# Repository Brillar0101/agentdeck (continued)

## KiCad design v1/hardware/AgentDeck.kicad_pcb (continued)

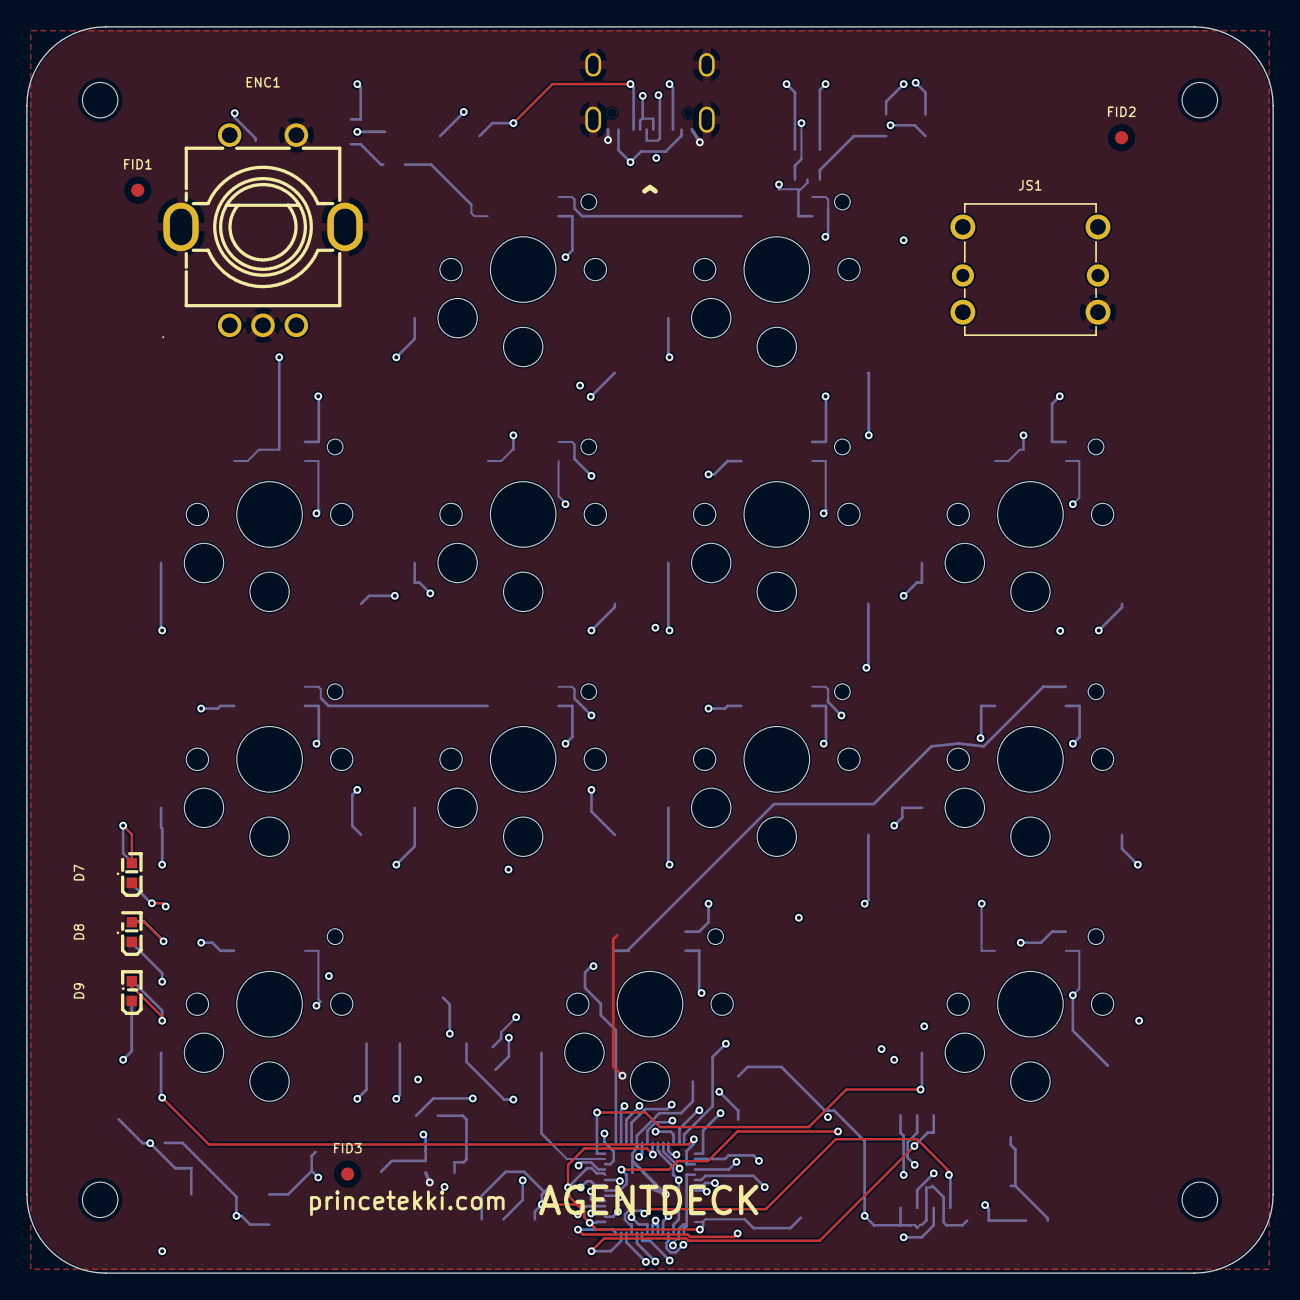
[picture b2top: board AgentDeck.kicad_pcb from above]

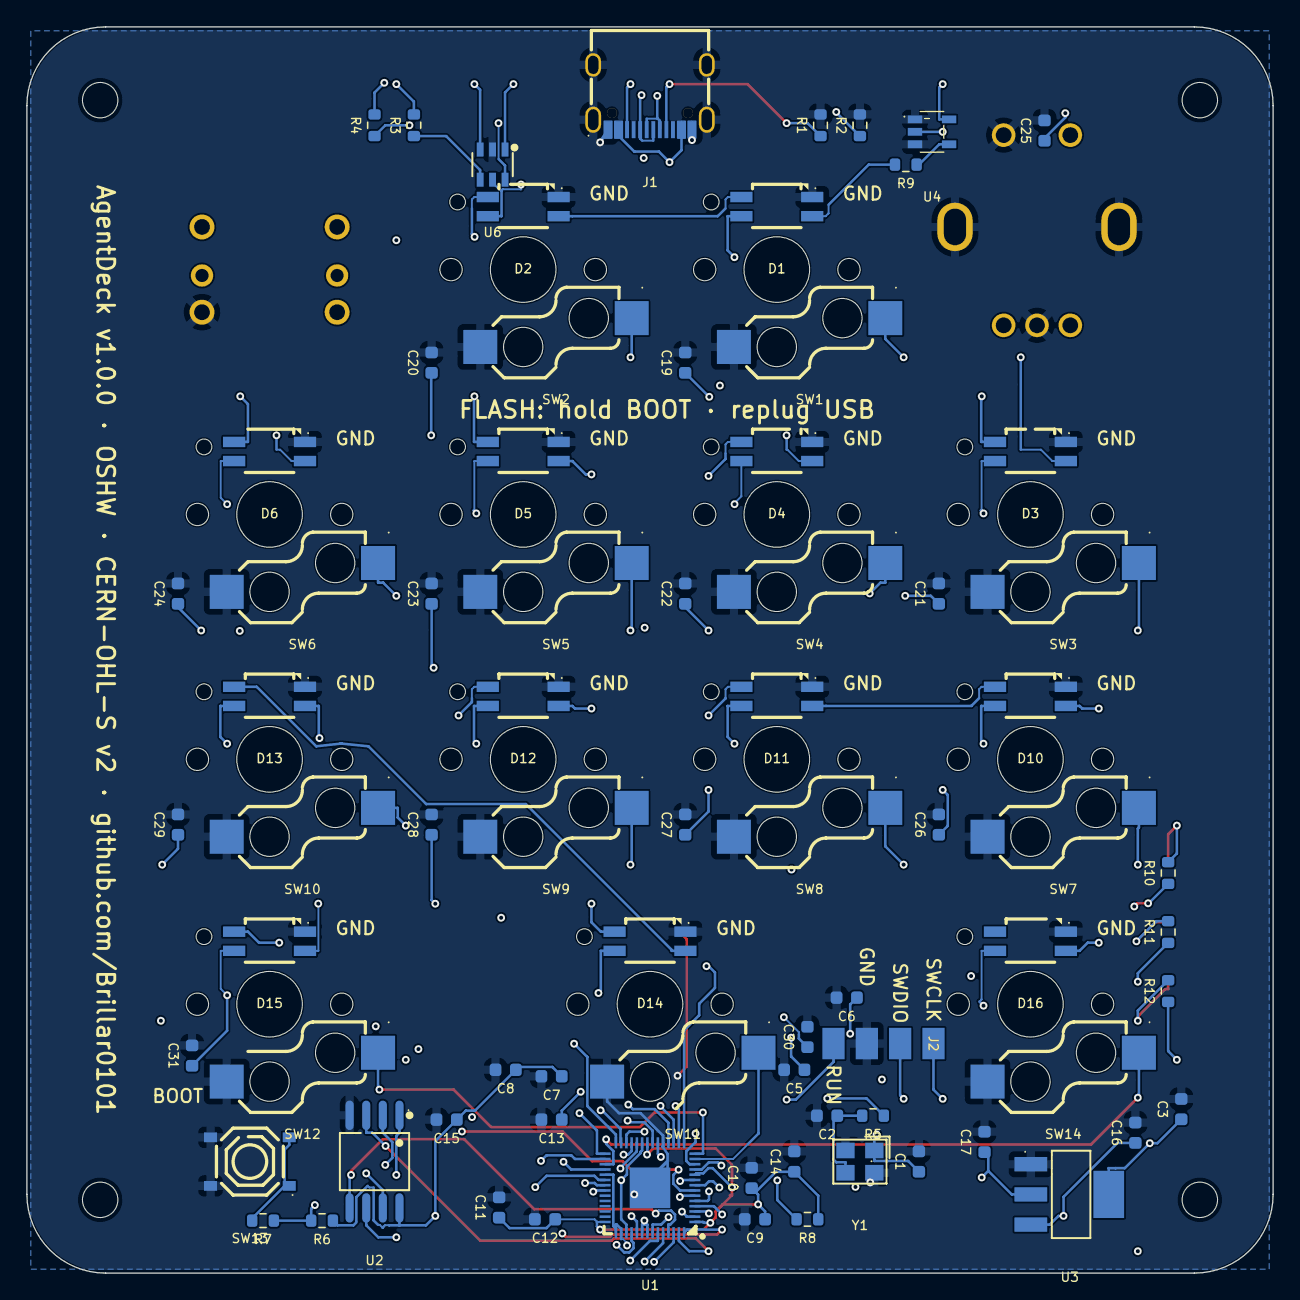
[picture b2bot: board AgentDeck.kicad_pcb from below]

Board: 4 copper layers, 95.0 x 95.0 mm, 101 parts (76 on the bottom side), 67 nets.

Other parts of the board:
D16: LED-SMD_4P-L3.2-W2.8-LS5.9_SK6812MINI-E
FID1, FID2, FID3: Fiducial_1mm_Mask2mm
KEY1, KEY2, KEY3, KEY4, KEY5, KEY6, KEY7, KEY8, KEY9, KEY10, KEY11, KEY12, KEY14: ChocSwitch; KeyOutline
MH1, MH2, MH3, MH4: M2.5; MountingHole_M2.5
SW14: CONN-SMD_HOTPLUGPAKAGE__C9900010116

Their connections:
GND: D16.1, SW14.2; also elsewhere on the board
LED_D13: D16.2; also elsewhere on the board
TOUCH: SW14.1; also elsewhere on the board
VBUS: D16.3; also elsewhere on the board

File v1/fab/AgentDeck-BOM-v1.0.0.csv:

Item,Designators,Qty,Value,Footprint,Supplier,Supplier PN,MPN,Status,Notes
1,"C10,C11,C12,C15,C19,C20,C21,C22,C23,C24,C25,C26,C27,C28,C29,C3,C30,C31,C5,C6,C7,C8,C9",23,100nF 50V X7R,C_0603,LCSC,C14663,CC0603KRX7R9BB104,In cart,
2,"D1,D2,D3,D4,D5,D6,D10,D11,D12,D13,D14,D15,D16",13,SK6812MINI-E RGB,LED-SMD_4P-3.2x2.8,LCSC,C5149201,SK6812MINI-E,In cart,"MOQ 5; ordered 15. Reverse-mount under keycap"
3,"R5,R7,R10,R11,R12",5,1k 1% 0603,R_0603,LCSC,C21190,0603WAF1001T5E,In cart,MOQ 100
4,"D7,D8,D9",3,Red LED 0603,LED-SMD_1.6x0.8,LCSC,C2286,KT-0603R,In cart,
5,"C16,C17",2,10uF 10V X5R 0603,C_0603,LCSC,C19702,CL10A106KP8NNNC,In cart,"MOQ 20. NOT the 0805 C15850 already in cart - package differs"
6,"C1,C2",2,15pF 50V C0G 0603,C_0603,LCSC,C1644,CL10C150JB8NNNC,In cart,MOQ 50. Crystal load caps
7,"C13,C14",2,1uF 0603,C_0603,LCSC,C128624,CC0603KRX5R9BB105,Already in cart,"Equivalent to BOM's C15849 - same value and package"
8,"R3,R4",2,27R 1% 0603,R_0603,LCSC,C25190,0603WAF270JT5E,In cart,"CORRECTED 2026-08-10: old BOM listed C22967 which is 27k - USB would not enumerate"
9,"R1,R2",2,5.1k 1% 0603,R_0603,LCSC,C23186,0603WAF5101T5E,Already in cart,USB-C CC pulldowns
10,R8,1,10k 1% 0603,R_0603,LCSC,C25804,0603WAF1002T5E,In cart - BACKORDERED,0 in stock; substitute any 10k 0603 if it blocks the order
11,R9,1,330R 1% 0603,R_0603,LCSC,C23138,0603WAF3300T5E,In cart,MOQ 100
12,U4,1,74AHCT1G125 buffer,SOT-23-5,LCSC,C7484,SN74AHCT1G125DBVR,In cart,MOQ 5. LED data level shift
13,Y1,1,12MHz crystal,CRYSTAL-SMD_3.2x2.5,LCSC,C20625731,ABM8-272-T3,In cart,MOQ 5
14,U3,1,AMS1117-3.3 LDO,SOT-223-3,LCSC,C6186,AMS1117-3.3,In cart,"MOQ 5. NOT the ME6211 C82942 in cart - different package"
15,SW13,1,Tact switch BOOTSEL,SW-SMD_5.1x5.1,LCSC,C318884,TS-1187A-B-A-B,Already in cart,
16,ENC1,1,EC11 rotary encoder,SW-TH_EC11E1820402,LCSC,C361165,EC11E1834403,In cart,"NOTE: LCSC ships the -1834403 variant; footprint is named for -1820402. Check shaft length against the case"
17,U1,1,RP2040,LQFN-56 7x7,LCSC,C2040,RP2040,In cart,
18,J1,1,USB-C receptacle,TYPE-C-31-M-12,LCSC,C165948,TYPE-C-31-M-12,Already in cart,
19,U6,1,USBLC6-2SC6 ESD,SOT-23-6,LCSC,C7519,USBLC6-2SC6,Already in cart,
20,U2,1,W25Q128JVSIQ 16MB flash,SOIC-8,LCSC,C97521,W25Q128JVSIQ,In cart,
21,"SW1,SW2,SW3,SW4,SW5,SW6,SW7,SW8,SW9,SW10,SW11,SW12,SW14",13,Kailh Choc hot-swap socket,CONN-SMD_HOTPLUGPAKAGE,AliExpress,,CPG135001S30,NOT ON LCSC,"LCSC C5333465 discontinued - 'Not Available'. Kailh Choc V1 sockets, ubiquitous on AliExpress"
22,JS1,1,5-way navigation switch,SKQUCAA010 (THT),AliExpress,,SKQUCAA010,NOT ON LCSC,"Also Newark 59M1983 / Farnell 1435775. DigiKey does not stock it. LCSC's C139794 (SKRHABE010) would need a new footprint AND a case change"
23,"SW1-SW12,SW14",13,Kailh Choc V1 switch,plugs into socket,AliExpress,,,Not a PCB part,Never an LCSC line - keyboard vendor only
24,"SW1-SW12,SW14",13,Choc keycap,n/a,AliExpress,,,Not a PCB part,Keyboard vendor
25,MH1-MH4,4,M2.5 x 8mm button-head screw (ISO 7380),n/a,AliExpress,,,Not a PCB part,"Case hardware. Passes lid 2.9mm shaft + counterbore, PCB 2.7mm hole, into heat-set insert below. Button head (4.7mm dia x 1.3mm) - NOT socket cap (2.5mm head too tall for the 3.9mm lid)"
26,MH1-MH4,4,M2.5 brass heat-set insert (4.0mm OD x 5.0mm),n/a,AliExpress,,,Not a PCB part,"The 'nut' the screw threads into. Melts into the tray boss 3.6mm bore. Search 'M2.5 heat set insert 4mm OD'. Install with soldering iron"
27,MH1-MH4,4,Cover cap (printed),case-cover-plug.stl,3D print,,,Not a purchased part,"5.0mm dia x 1.2mm printed plug that hides the screw head in the counterbore. Print 4 from enclosure/case-cover-plug.stl"

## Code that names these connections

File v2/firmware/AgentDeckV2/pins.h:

// AgentDeck V2 pin map - matches v2/tools/gen_schematic.py PINOUT table.
// Diff against the generator's printed table whenever either side changes.
#pragma once

// 4x5 key matrix (COL2ROW: switch->diode anode, cathode->row)
constexpr int ROW_PINS[4] = {4, 5, 6, 7};
constexpr int COL_PINS[5] = {10, 11, 12, 13, 14};
constexpr int NUM_ROWS = 4, NUM_COLS = 5, NUM_KEYS = 20;

// Peripherals
constexpr int PIN_LED_DATA = 21;   // SK6812 chain via AHCT125 (VSYS_SW rail)
constexpr int NUM_LEDS = 20;
constexpr int PIN_I2C_SDA = 8;     // OLED SSD1315 @0x3C
constexpr int PIN_I2C_SCL = 9;
constexpr int PIN_ENC_A = 40;
constexpr int PIN_ENC_B = 41;
constexpr int PIN_ENC_SW = 42;
constexpr int PIN_VBAT_ADC = 2;    // ADC1_CH1, 100k/47k divider
constexpr int PIN_CHRG = 47;       // TP4056 CHRG (active low)
constexpr int PIN_STDBY = 48;      // TP4056 STDBY (active low)

// Alps SKQUCAA010 5-way joystick, active low with internal pullups, COM->GND
constexpr int PIN_JOY_UP = 15, PIN_JOY_LEFT = 16, PIN_JOY_DOWN = 17,
              PIN_JOY_RIGHT = 18, PIN_JOY_CTR = 1;

// Battery divider: Vbat = ADC * (100+47)/47
constexpr float VBAT_DIVIDER = 147.0f / 47.0f;

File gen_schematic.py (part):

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                25: "37", 26: "38", 27: "39", 28: "40", 29: "41"}
    for k in range(12):
        spec[gpio_pin[k]] = ("lbl", f"K{k+1}")
    spec[gpio_pin[12]] = ("lbl", "ENC_A")
    spec[gpio_pin[13]] = ("lbl", "ENC_B")
    spec[gpio_pin[14]] = ("lbl", "ENC_SW")
    for i, d in enumerate(["JOY_A", "JOY_B", "JOY_C", "JOY_D", "JOY_CTR"]):
        spec[gpio_pin[15 + i]] = ("lbl", d)
    spec[gpio_pin[20]] = ("lbl", "TOUCH")
    spec[gpio_pin[21]] = ("lbl", "LED_DATA")
    spec[gpio_pin[22]] = ("lbl", "AUX1")
    spec[gpio_pin[23]] = ("lbl", "AUX2")
    spec[gpio_pin[24]] = ("lbl", "AUX3")
    for g in range(25, 30):
        spec[gpio_pin[g]] = ("nc",)
    part_taps(mcu, "U1", "RP2040", mx, my, spec)
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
